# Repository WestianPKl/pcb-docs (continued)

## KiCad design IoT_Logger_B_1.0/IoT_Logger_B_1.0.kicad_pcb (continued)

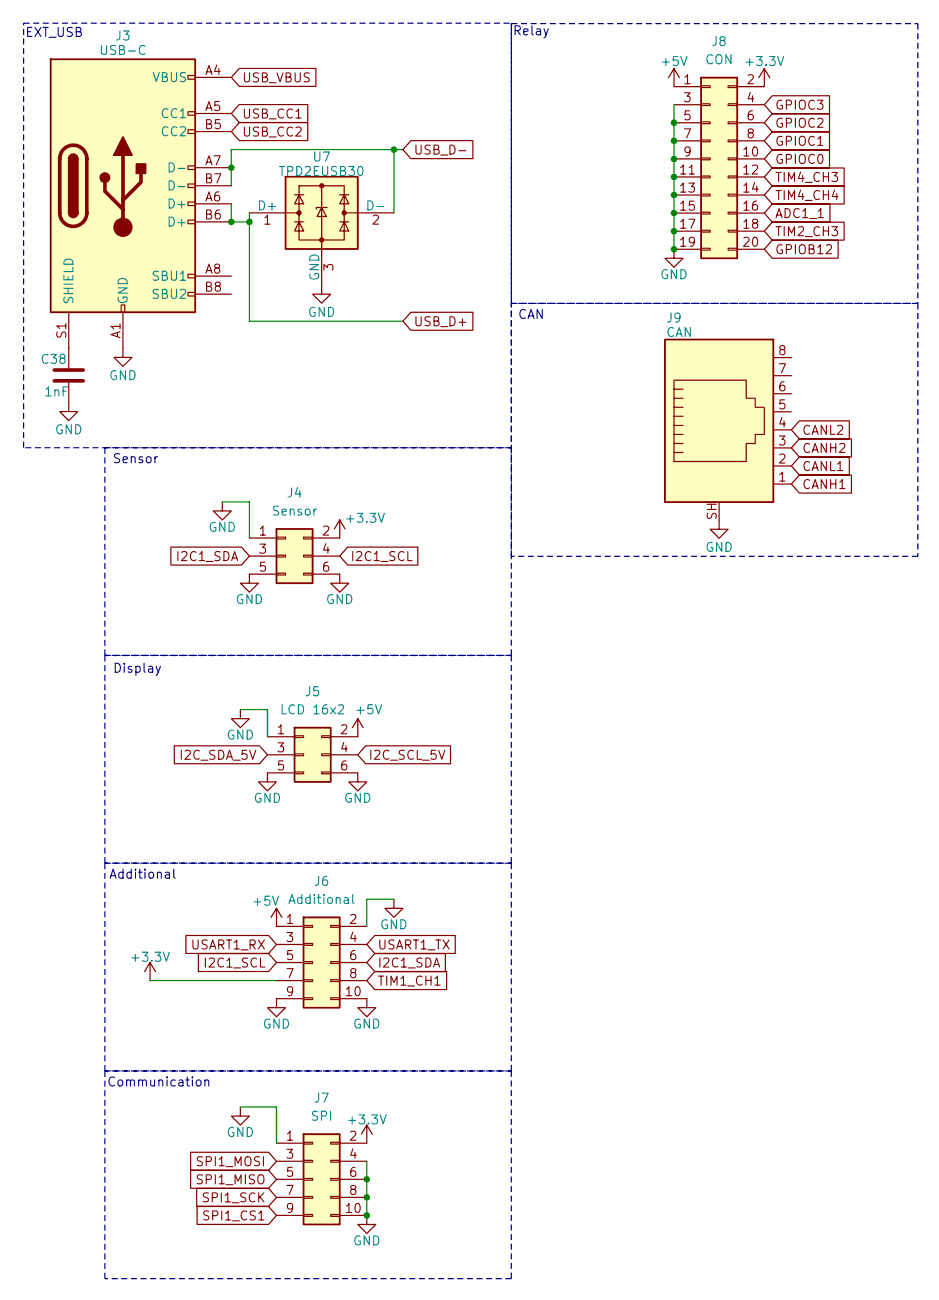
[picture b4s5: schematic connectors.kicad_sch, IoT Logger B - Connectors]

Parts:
C38: 1nF; C_0603_1608Metric
J3: USB-C; USB_C_Receptacle_GCT_USB4085
J4: Sensor; IDC-Header_2x03_P2.54mm_Vertical
J5: LCD 16x2; IDC-Header_2x03_P2.54mm_Vertical
J6: Additional; PinSocket_2x05_P2.54mm_Vertical
J7: SPI; IDC-Header_2x05_P2.54mm_Vertical
J8: CON; PinSocket_2x10_P2.54mm_Vertical
J9: CAN; RJ45_Amphenol_RJHSE5380_SHORT
U7: TPD2EUSB30; Texas_DRT-3

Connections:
+3.3V: J4.2, J6.7, J7.2, J8.2; also elsewhere on the board
+5V: J5.2, J6.1, J8.1; also elsewhere on the board
ADC1_1: J8.16; also elsewhere on the board
CANH1: J9.1; also elsewhere on the board
CANH2: J9.3
CANL1: J9.2; also elsewhere on the board
CANL2: J9.4
GND: C38.2, J3.A1 (GND), J3.A12 (GND), J3.B1 (GND), J3.B12 (GND), J4.1, J4.5, J4.6, J5.1, J5.5, J5.6, J6.2, J6.9, J6.10, J7.1, J7.4, J7.6, J7.8, J7.10, J8.3, J8.5, J8.7, J8.9, J8.11, J8.13, J8.15, J8.17, J8.19, J9.SH, U7.3 (GND); also elsewhere on the board
GPIOB12: J8.20; also elsewhere on the board
GPIOC0: J8.10; also elsewhere on the board
GPIOC1: J8.8; also elsewhere on the board
GPIOC2: J8.6; also elsewhere on the board
GPIOC3: J8.4; also elsewhere on the board
I2C1_SCL: J4.4, J6.5; also elsewhere on the board
I2C1_SDA: J4.3, J6.6; also elsewhere on the board
I2C_SCL_5V: J5.4; also elsewhere on the board
I2C_SDA_5V: J5.3; also elsewhere on the board
unnamed: C38.1, J3.S1 (SHIELD)
SPI1_CS1: J7.9; also elsewhere on the board
SPI1_MISO: J7.5; also elsewhere on the board
SPI1_MOSI: J7.3; also elsewhere on the board
SPI1_SCK: J7.7; also elsewhere on the board
TIM1_CH1: J6.8; also elsewhere on the board
TIM2_CH3: J8.18; also elsewhere on the board
TIM4_CH3: J8.12; also elsewhere on the board
TIM4_CH4: J8.14; also elsewhere on the board
USART1_RX: J6.3; also elsewhere on the board
USART1_TX: J6.4; also elsewhere on the board
USB_CC1: J3.A5 (CC1); also elsewhere on the board
USB_CC2: J3.B5 (CC2); also elsewhere on the board
USB_D+: J3.A6 (D+), J3.B6 (D+), U7.1 (D+); also elsewhere on the board
USB_D-: J3.A7 (D-), J3.B7 (D-), U7.2 (D-); also elsewhere on the board
USB_VBUS: J3.A4 (VBUS), J3.A9 (VBUS), J3.B4 (VBUS), J3.B9 (VBUS); also elsewhere on the board

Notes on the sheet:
EXT_USB
Additional
Sensor
Relay
CAN
Display
Communication

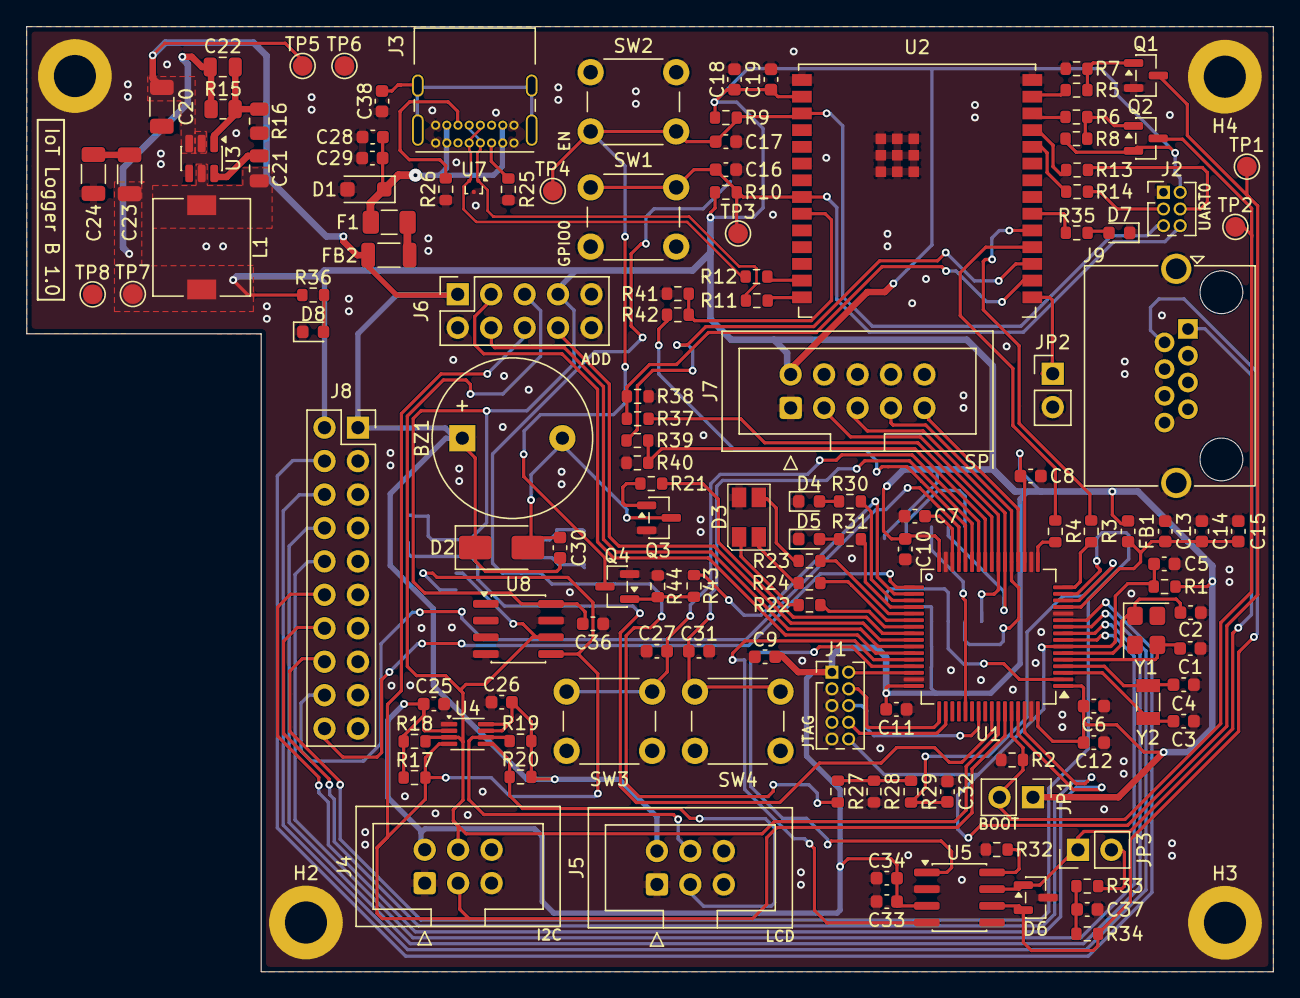
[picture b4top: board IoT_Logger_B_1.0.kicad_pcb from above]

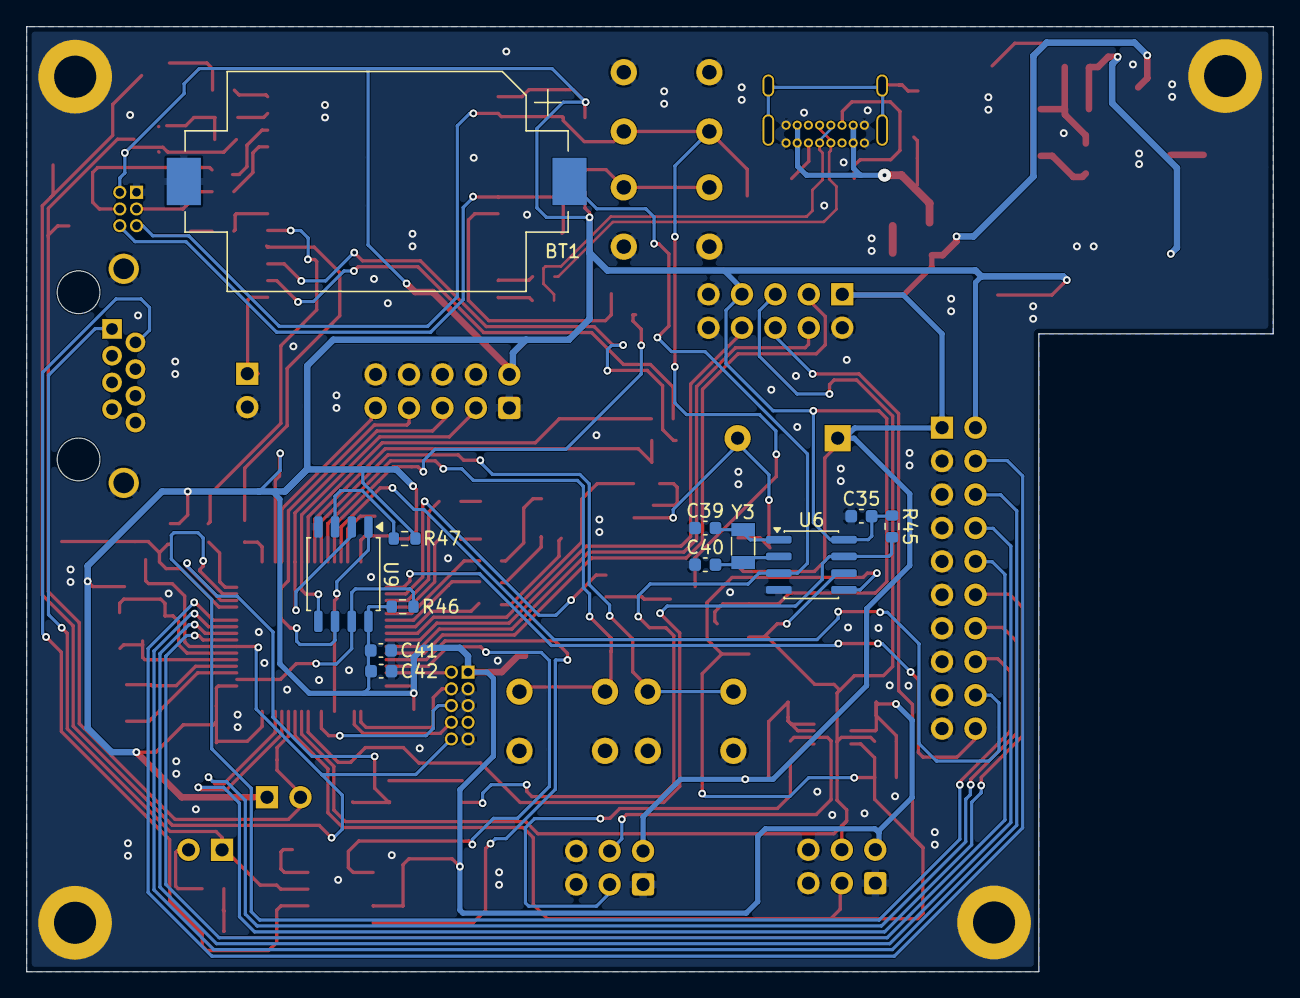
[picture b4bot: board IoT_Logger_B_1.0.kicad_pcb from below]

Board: 2 copper layers, 94.7 x 71.8 mm, 147 parts (12 on the bottom side), 105 nets.

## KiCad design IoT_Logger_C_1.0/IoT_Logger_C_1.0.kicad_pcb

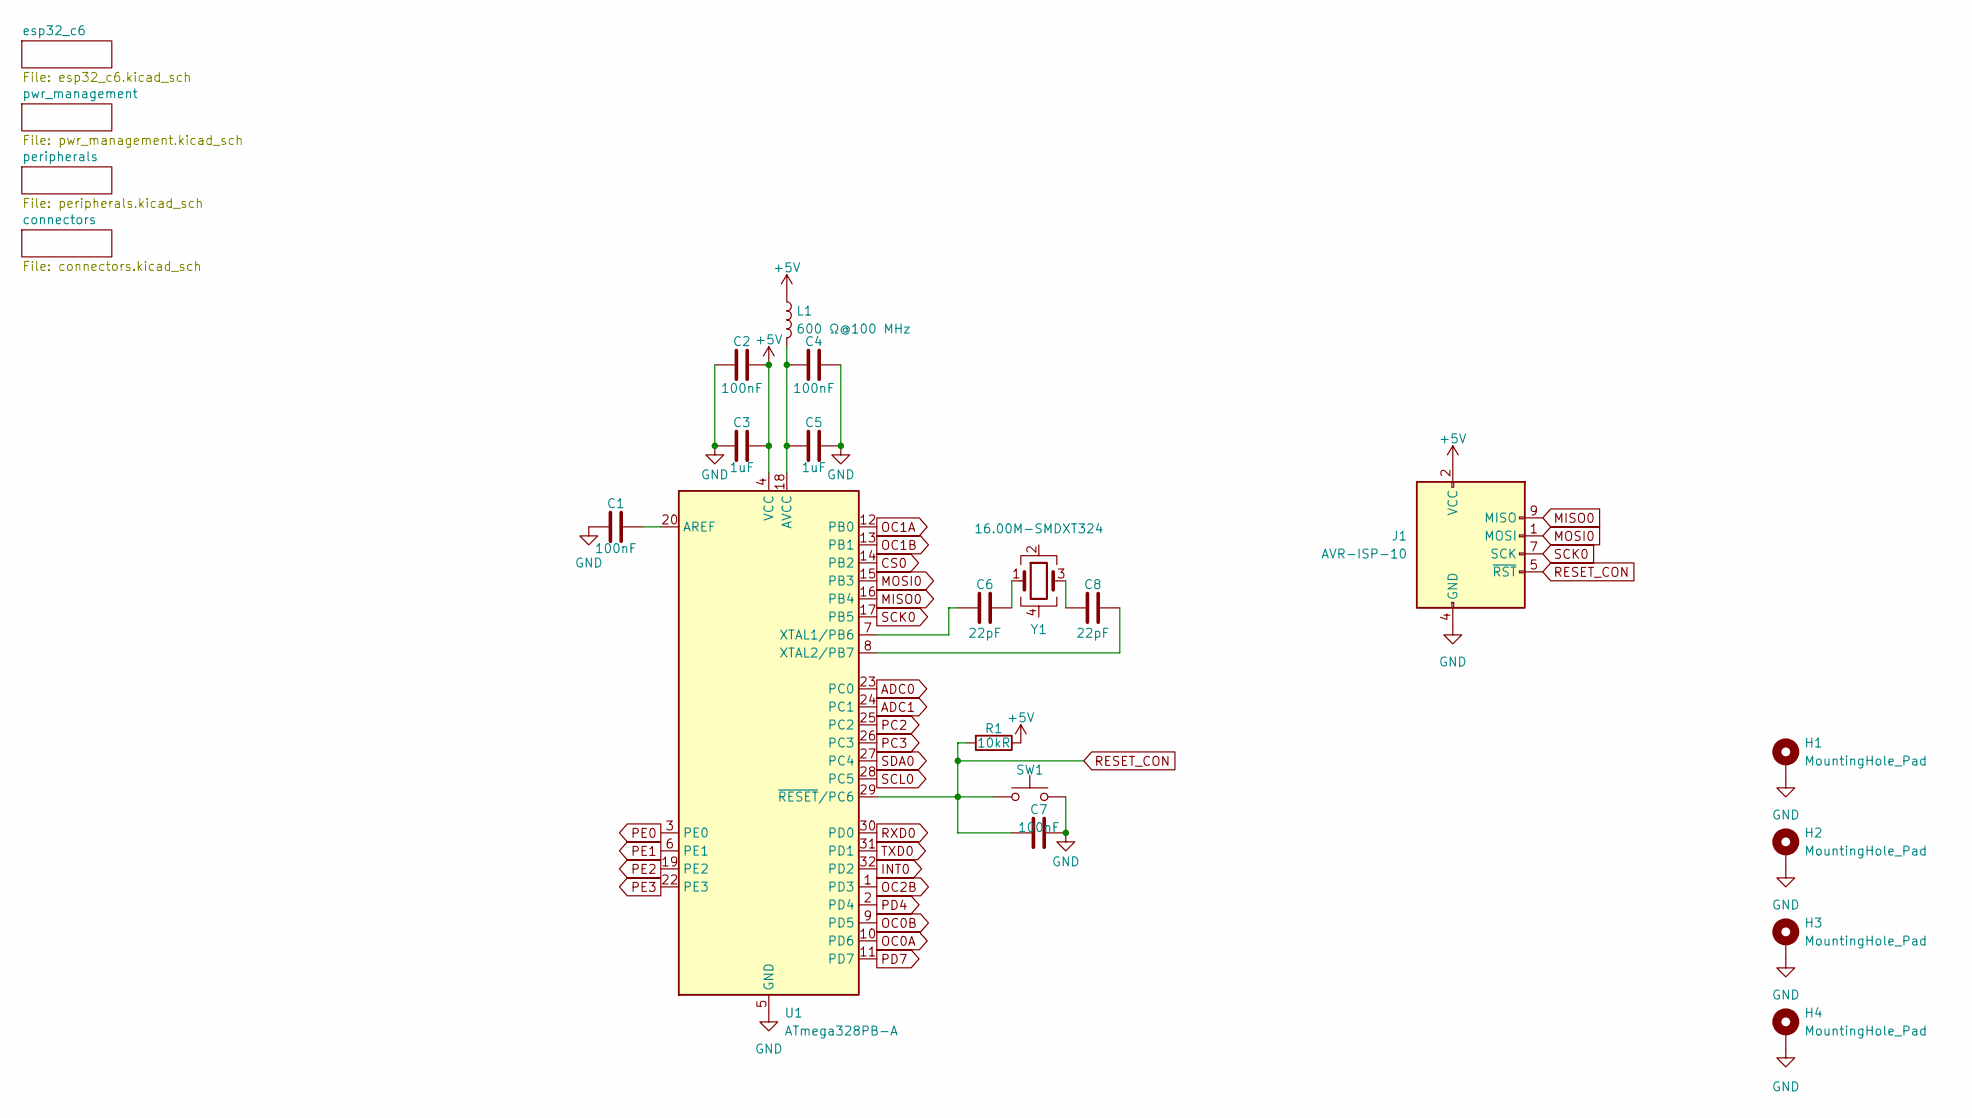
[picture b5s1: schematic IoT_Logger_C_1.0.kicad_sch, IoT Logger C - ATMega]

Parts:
C1, C2, C4, C7: 100nF; C_0603_1608Metric
C3, C5: 1uF; C_0603_1608Metric
C6, C8: 22pF; C_0603_1608Metric
H1, H2, H3, H4: MountingHole_Pad; MountingHole_3.2mm_M3_DIN965_Pad
J1: AVR-ISP-10; IDC-Header_2x05_P2.54mm_Vertical
L1: 600 Ω@100 MHz; L_0603_1608Metric
R1: 10kR; R_0603_1608Metric
SW1: Tact Switch 6x6mm / 13mm; SW_PUSH_6mm
U1: ATmega328PB-A; TQFP-32_7x7mm_P0.8mm
Y1: 16.00M-SMDXT324; Crystal_SMD_3225-4Pin_3.2x2.5mm

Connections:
+5V: C2.2, C3.2, J1.2 (VCC), L1.1, R1.1, U1.4 (VCC); also elsewhere on the board
ADC0: U1.23 (PC0); also elsewhere on the board
ADC1: U1.24 (PC1); also elsewhere on the board
CS0: U1.14 (PB2); also elsewhere on the board
GND: C1.1, C2.1, C3.1, C4.2, C5.2, C7.2, H1.1, H2.1, H3.1, H4.1, J1.4 (GND), J1.6 (GND), J1.8 (GND), J1.10 (GND), SW1.2, U1.5 (GND), U1.21 (GND); also elsewhere on the board
INT0: U1.32 (PD2); also elsewhere on the board
MISO0: J1.9 (MISO), U1.16 (PB4); also elsewhere on the board
MOSI0: J1.1 (MOSI), U1.15 (PB3); also elsewhere on the board
unnamed: C6.2, Y1.1
unnamed: C8.1, Y1.3
unnamed: C1.2, U1.20 (AREF)
unnamed: C4.1, C5.1, L1.2, U1.18 (AVCC)
unnamed: C6.1, U1.7 (XTAL1/PB6)
unnamed: C8.2, U1.8 (XTAL2/PB7)
OC0A: U1.10 (PD6); also elsewhere on the board
OC0B: U1.9 (PD5); also elsewhere on the board
OC1A: U1.12 (PB0); also elsewhere on the board
OC1B: U1.13 (PB1)
OC2B: U1.1 (PD3); also elsewhere on the board
PC2: U1.25 (PC2); also elsewhere on the board
PC3: U1.26 (PC3); also elsewhere on the board
PD4: U1.2 (PD4); also elsewhere on the board
PD7: U1.11 (PD7); also elsewhere on the board
PE0: U1.3 (PE0); also elsewhere on the board
PE1: U1.6 (PE1); also elsewhere on the board
PE2: U1.19 (PE2); also elsewhere on the board
PE3: U1.22 (PE3); also elsewhere on the board
RESET_CON: C7.1, J1.5 (~RST), R1.2, SW1.1, U1.29 (~RESET/PC6); also elsewhere on the board
RXD0: U1.30 (PD0); also elsewhere on the board
SCK0: J1.7 (SCK), U1.17 (PB5); also elsewhere on the board
SCL0: U1.28 (PC5); also elsewhere on the board
SDA0: U1.27 (PC4); also elsewhere on the board
TXD0: U1.31 (PD1); also elsewhere on the board

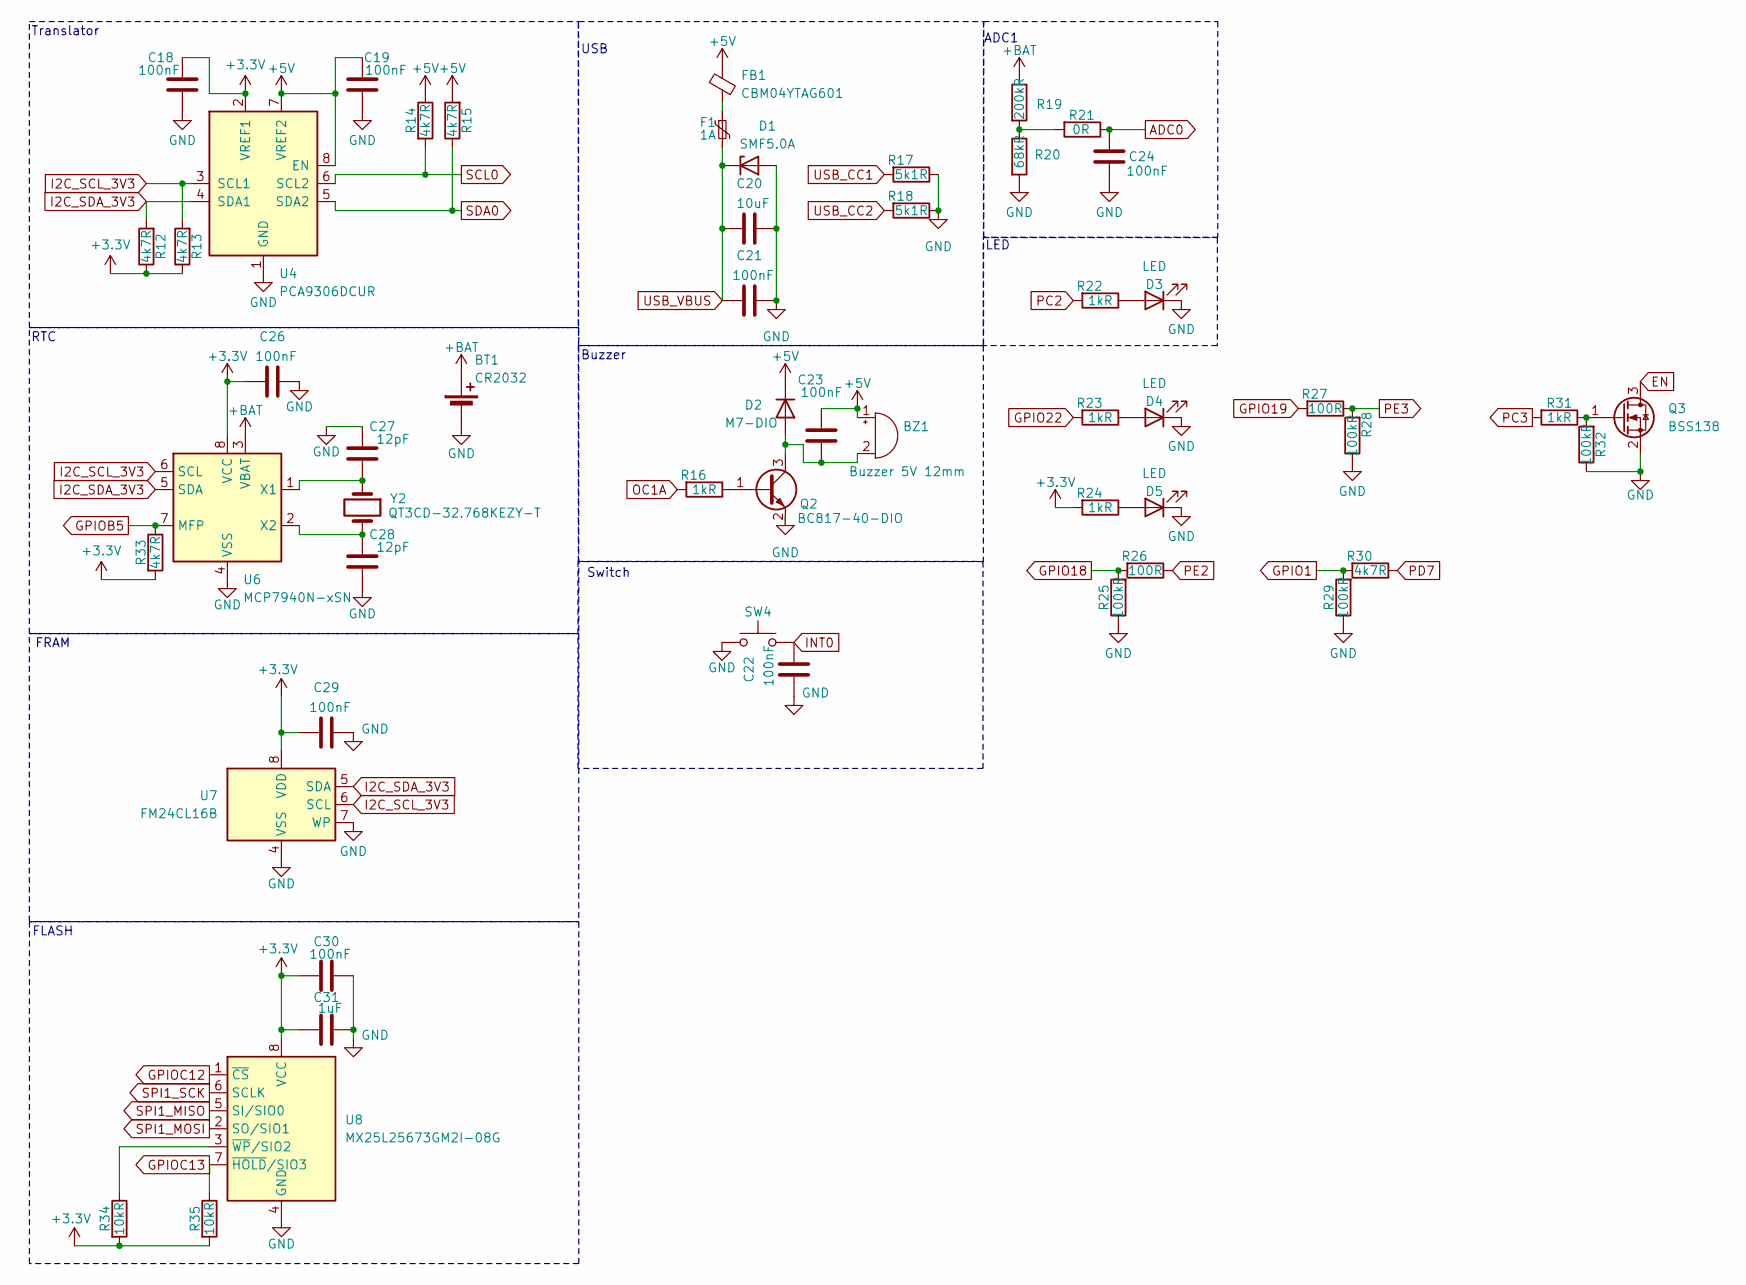
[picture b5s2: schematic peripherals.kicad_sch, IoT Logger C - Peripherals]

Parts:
BT1: CR2032; BatteryHolder_Keystone_1060_1x2032
BZ1: Buzzer 5V 12mm; Buzzer_12x9.5RM7.6
C18, C19, C21, C22, C23, C24, C26, C29, C30: 100nF; C_0603_1608Metric
C20: 10uF; C_0603_1608Metric
C27, C28: 12pF; C_0603_1608Metric
C31: 1uF; C_0603_1608Metric
D1: SMF5.0A; D_SOD-123F
D2: M7-DIO; D_SMA
D3, D4, D5: LED; LED_0603_1608Metric
F1: 1A; Fuse_1206_3216Metric
FB1: CBM04YTAG601; L_1206_3216Metric
Q2: BC817-40-DIO; SOT-23
Q3: BSS138; SOT-23
R12, R13, R14, R15, R30, R33: 4k7R; R_0603_1608Metric
R16, R22, R23, R24, R31: 1kR; R_0603_1608Metric
R17, R18: 5k1R; R_0603_1608Metric
R19: 200kR; R_0603_1608Metric
R20: 68kR; R_0603_1608Metric
R21: 0R; R_0603_1608Metric
R25, R28, R29, R32: 100kR; R_0603_1608Metric
R26, R27: 100R; R_0603_1608Metric
R34, R35: 10kR; R_0603_1608Metric
SW4: Tact Switch 6x6mm / 13mm; SW_PUSH_6mm
U4: PCA9306DCUR; VSSOP-8_2.3x2mm_P0.5mm
U6: MCP7940N-xSN; SOIC-8_3.9x4.9mm_P1.27mm
U7: FM24CL16B; SOIC-8_3.9x4.9mm_P1.27mm
U8: MX25L25673GM2I-08G; SOIC-8_5.3x5.3mm_P1.27mm
Y2: QT3CD-32.768KEZY-T; Crystal_SMD_3215-2Pin_3.2x1.5mm

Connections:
+3.3V: C18.1, C26.2, C29.2, C30.2, C31.2, R12.1, R13.1, R24.2, R33.2, R34.2, R35.2, U4.2 (VREF1), U6.8 (VCC), U7.8 (VDD), U8.8 (VCC); also elsewhere on the board
+5V: BZ1.1 (+), C19.1, C23.2, D2.1 (K), FB1.1, R14.1, R15.2, U4.7 (VREF2), U4.8 (EN); also elsewhere on the board
+BAT: BT1.1 (+), R19.1, U6.3 (VBAT)
ADC0: C24.1, R21.1; also elsewhere on the board
EN: Q3.3 (D); also elsewhere on the board
GND: BT1.2 (-), C18.2, C19.2, C20.1, C21.1, C22.2, C24.2, C26.1, C27.2, C28.1, C29.1, C30.1, C31.1, D1.2 (A), D3.1 (K), D4.1 (K), D5.1 (K), Q2.2 (E), Q3.2 (S), R17.1, R18.1, R20.2, R25.1, R28.1, R29.1, R32.1, SW4.1, U4.1 (GND), U6.4 (VSS), U7.4 (VSS), U7.7 (WP), U8.4 (GND); also elsewhere on the board
GPIO1: R29.2, R30.2; also elsewhere on the board
GPIO18: R25.2, R26.2; also elsewhere on the board
GPIO19: R27.2; also elsewhere on the board
GPIO22: R23.2; also elsewhere on the board
GPIOB5: R33.1, U6.7 (MFP)
I2C_SCL_3V3: R13.2, U4.3 (SCL1), U6.6 (SCL), U7.6 (SCL); also elsewhere on the board
I2C_SDA_3V3: R12.2, U4.4 (SDA1), U6.5 (SDA), U7.5 (SDA); also elsewhere on the board
INT0: C22.1, SW4.2; also elsewhere on the board
unnamed: BZ1.2 (-), C23.1, D2.2 (A), Q2.3 (C)
unnamed: D3.2 (A), R22.1
unnamed: D4.2 (A), R23.1
unnamed: D5.2 (A), R24.1
unnamed: F1.1, FB1.2
unnamed: Q2.1 (B), R16.1
unnamed: Q3.1 (G), R31.1, R32.2
unnamed: R19.2, R20.1, R21.2
unnamed: R34.1, U8.3 (~WP/SIO2)
unnamed: R35.1, U8.7 (~HOLD/SIO3)
unnamed: C27.1, U6.1 (X1), Y2.1
unnamed: C28.2, U6.2 (X2), Y2.2
OC1A: R16.2; also elsewhere on the board
PC2: R22.2; also elsewhere on the board
PC3: R31.2; also elsewhere on the board
PD7: R30.1; also elsewhere on the board
PE2: R26.1; also elsewhere on the board
PE3: R27.1, R28.2; also elsewhere on the board
SCL0: R14.2, U4.6 (SCL2); also elsewhere on the board
SDA0: R15.1, U4.5 (SDA2); also elsewhere on the board
USB_CC1: R17.2; also elsewhere on the board
USB_CC2: R18.2; also elsewhere on the board
USB_VBUS: C20.2, C21.2, D1.1 (K), F1.2; also elsewhere on the board

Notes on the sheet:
USB
RTC
FRAM
FLASH
Switch
Translator
Buzzer
ADC1
LED

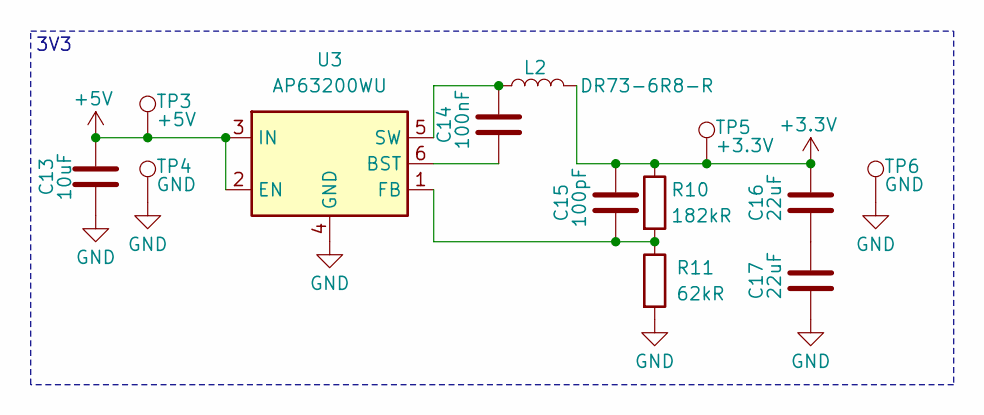
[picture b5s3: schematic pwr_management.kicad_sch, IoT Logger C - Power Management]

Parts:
C13: 10uF; C_1206_3216Metric
C14: 100nF; C_0805_2012Metric
C15: 100pF; C_0805_2012Metric
C16, C17: 22uF; C_1206_3216Metric
L2: DR73-6R8-R; L_7.3x7.3_H3.5
R10: 182kR; R_0805_2012Metric
R11: 62kR; R_0805_2012Metric
TP3: +5V; TestPoint_Pad_D1.5mm
TP4, TP6: GND; TestPoint_Pad_D1.5mm
TP5: +3.3V; TestPoint_Pad_D1.5mm
U3: AP63200WU; TSOT-23-6

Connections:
+3.3V: C15.1, C16.1, L2.2, R10.1, TP5.1; also elsewhere on the board
+5V: C13.1, TP3.1, U3.2 (EN), U3.3 (IN); also elsewhere on the board
GND: C13.2, C17.2, R11.2, TP4.1, TP6.1, U3.4 (GND); also elsewhere on the board
unnamed: C16.2, C17.1
unnamed: C14.2, U3.6 (BST)
unnamed: C15.2, R10.2, R11.1, U3.1 (FB)
unnamed: C14.1, L2.1, U3.5 (SW)

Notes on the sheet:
3V3

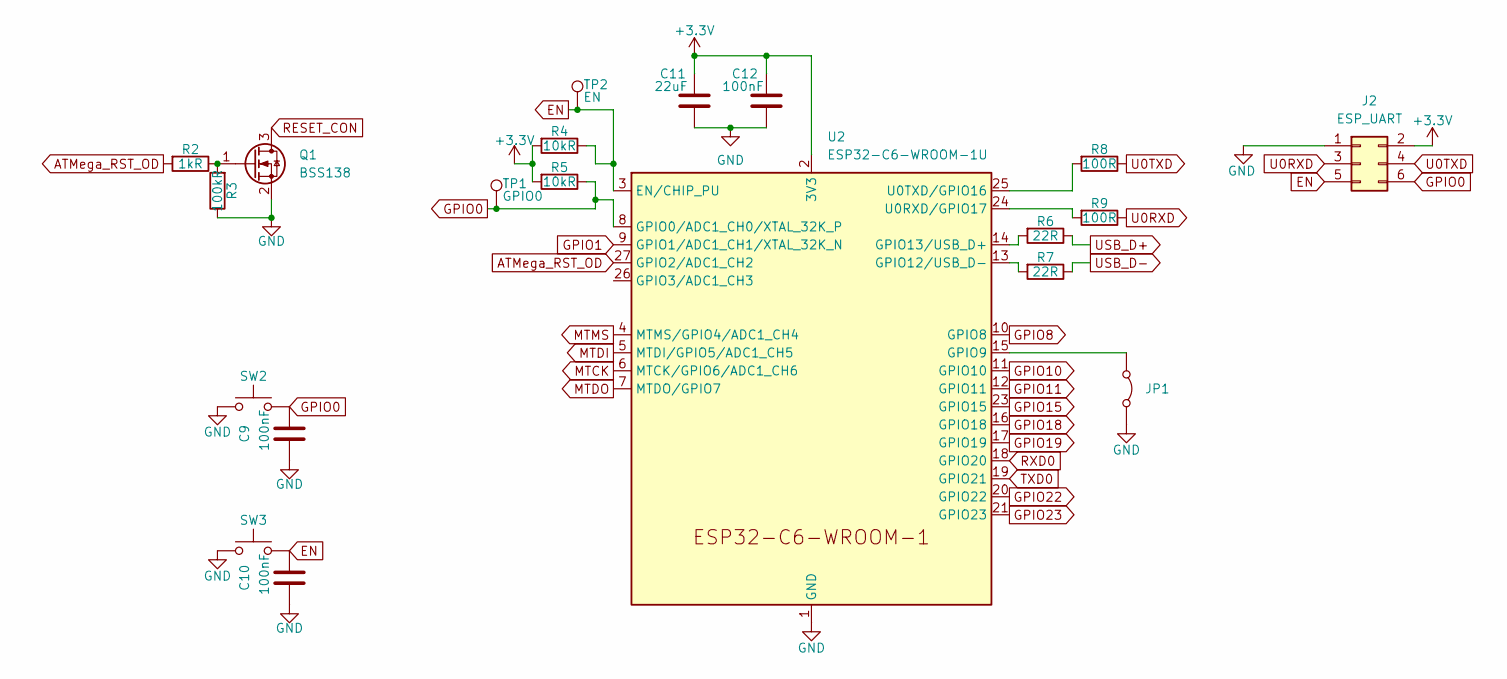
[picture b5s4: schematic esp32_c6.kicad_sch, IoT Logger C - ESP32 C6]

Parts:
C9, C10, C12: 100nF; C_0603_1608Metric
C11: 22uF; C_0603_1608Metric
J2: ESP_UART; PinHeader_2x03_P1.27mm_Vertical
JP1: Jumper_2_Bridged; PinHeader_1x02_P2.54mm_Vertical
Q1: BSS138; SOT-23
R2: 1kR; R_0603_1608Metric
R3: 100kR; R_0603_1608Metric
R4, R5: 10kR; R_0603_1608Metric
R6, R7: 22R; R_0603_1608Metric
R8, R9: 100R; R_0603_1608Metric
SW2, SW3: Tact Switch 6x6mm / 13mm; SW_PUSH_6mm
TP1: GPIO0; TestPoint_Pad_D1.5mm
TP2: EN; TestPoint_Pad_D1.5mm
U2: ESP32-C6-WROOM-1U

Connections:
+3.3V: C11.1, C12.1, J2.2, R4.2, R5.2, U2.2 (3V3); also elsewhere on the board
ATMega_RST_OD: R2.2, U2.27 (GPIO2/ADC1_CH2)
EN: C10.1, J2.5, R4.1, SW3.2, TP2.1, U2.3 (EN/CHIP_PU); also elsewhere on the board
GND: C9.2, C10.2, C11.2, C12.2, J2.1, JP1.2 (B), Q1.2 (S), R3.1, SW2.1, SW3.1, U2.1 (GND), U2.28 (GND), U2.29 (GND); also elsewhere on the board
GPIO0: C9.1, J2.6, R5.1, SW2.2, TP1.1, U2.8 (GPIO0/ADC1_CH0/XTAL_32K_P)
GPIO1: U2.9 (GPIO1/ADC1_CH1/XTAL_32K_N); also elsewhere on the board
GPIO8: U2.10 (GPIO8)
GPIO10: U2.11 (GPIO10)
GPIO11: U2.12 (GPIO11)
GPIO15: U2.23 (GPIO15)
GPIO18: U2.16 (GPIO18); also elsewhere on the board
GPIO19: U2.17 (GPIO19); also elsewhere on the board
GPIO22: U2.20 (GPIO22); also elsewhere on the board
GPIO23: U2.21 (GPIO23)
MTCK: U2.6 (MTCK/GPIO6/ADC1_CH6)
MTDI: U2.5 (MTDI/GPIO5/ADC1_CH5)
MTDO: U2.7 (MTDO/GPIO7)
MTMS: U2.4 (MTMS/GPIO4/ADC1_CH4)
unnamed: JP1.1 (A), U2.15 (GPIO9)
unnamed: Q1.1 (G), R2.1, R3.2
unnamed: R7.2, U2.13 (GPIO12/USB_D-)
unnamed: R6.2, U2.14 (GPIO13/USB_D+)
unnamed: R9.2, U2.24 (U0RXD/GPIO17)
unnamed: R8.2, U2.25 (U0TXD/GPIO16)
RESET_CON: Q1.3 (D); also elsewhere on the board
RXD0: U2.18 (GPIO20); also elsewhere on the board
TXD0: U2.19 (GPIO21); also elsewhere on the board
U0RXD: J2.3, R9.1
U0TXD: J2.4, R8.1
USB_D+: R6.1; also elsewhere on the board
USB_D-: R7.1; also elsewhere on the board

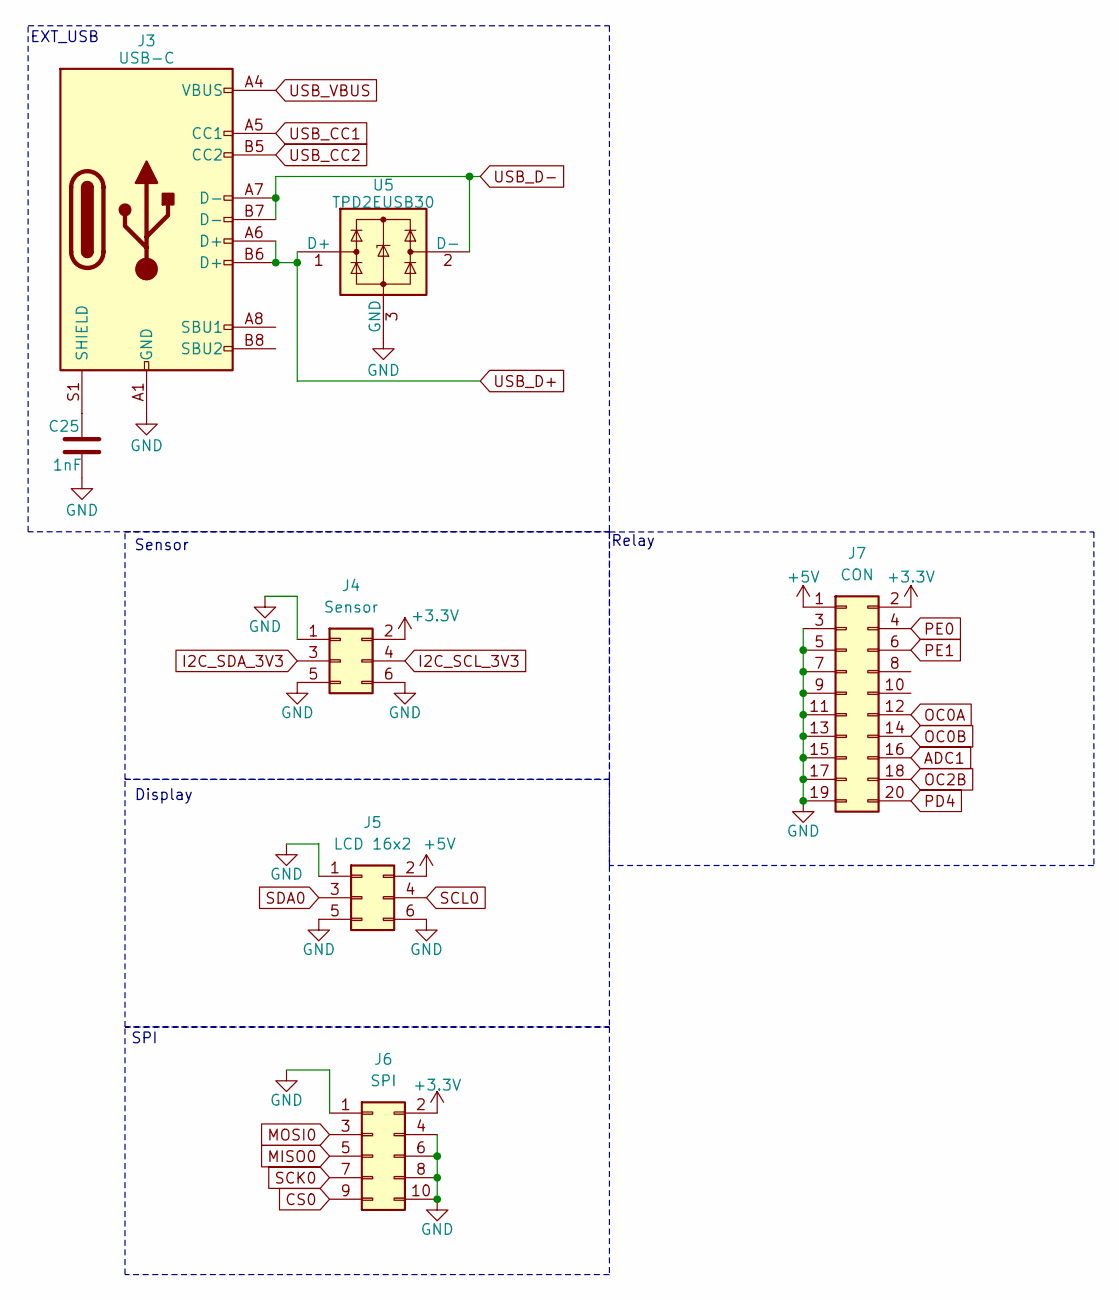
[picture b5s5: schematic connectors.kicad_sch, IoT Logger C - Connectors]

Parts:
C25: 1nF; C_0603_1608Metric
J3: USB-C; USB_C_Receptacle_GCT_USB4085
J4: Sensor; IDC-Header_2x03_P2.54mm_Vertical
J5: LCD 16x2; IDC-Header_2x03_P2.54mm_Vertical
J6: SPI; IDC-Header_2x05_P2.54mm_Vertical
J7: CON; PinSocket_2x10_P2.54mm_Vertical
U5: TPD2EUSB30; Texas_DRT-3

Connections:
+3.3V: J4.2, J6.2, J7.2; also elsewhere on the board
+5V: J5.2, J7.1; also elsewhere on the board
ADC1: J7.16; also elsewhere on the board
CS0: J6.9; also elsewhere on the board
GND: C25.2, J3.A1 (GND), J3.A12 (GND), J3.B1 (GND), J3.B12 (GND), J4.1, J4.5, J4.6, J5.1, J5.5, J5.6, J6.1, J6.4, J6.6, J6.8, J6.10, J7.3, J7.5, J7.7, J7.9, J7.11, J7.13, J7.15, J7.17, J7.19, U5.3 (GND); also elsewhere on the board
I2C_SCL_3V3: J4.4; also elsewhere on the board
I2C_SDA_3V3: J4.3; also elsewhere on the board
MISO0: J6.5; also elsewhere on the board
MOSI0: J6.3; also elsewhere on the board
unnamed: C25.1, J3.S1 (SHIELD)
OC0A: J7.12; also elsewhere on the board
OC0B: J7.14; also elsewhere on the board
OC2B: J7.18; also elsewhere on the board
PD4: J7.20; also elsewhere on the board
PE0: J7.4; also elsewhere on the board
PE1: J7.6; also elsewhere on the board
SCK0: J6.7; also elsewhere on the board
SCL0: J5.4; also elsewhere on the board
SDA0: J5.3; also elsewhere on the board
USB_CC1: J3.A5 (CC1); also elsewhere on the board
USB_CC2: J3.B5 (CC2); also elsewhere on the board
USB_D+: J3.A6 (D+), J3.B6 (D+), U5.1 (D+); also elsewhere on the board
USB_D-: J3.A7 (D-), J3.B7 (D-), U5.2 (D-); also elsewhere on the board
USB_VBUS: J3.A4 (VBUS), J3.A9 (VBUS), J3.B4 (VBUS), J3.B9 (VBUS); also elsewhere on the board

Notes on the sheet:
EXT_USB
Sensor
Relay
Display
SPI

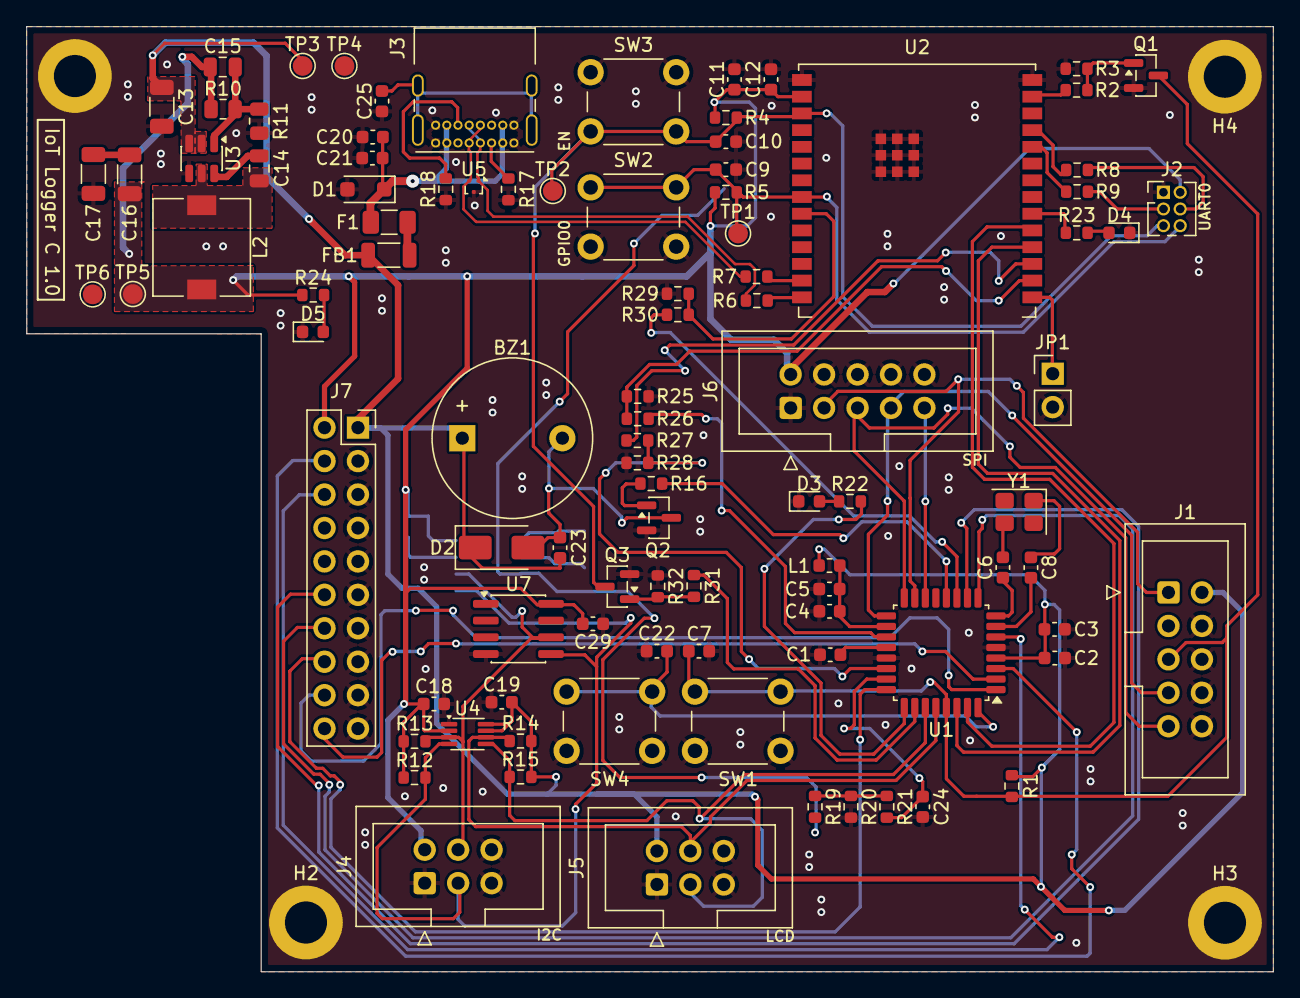
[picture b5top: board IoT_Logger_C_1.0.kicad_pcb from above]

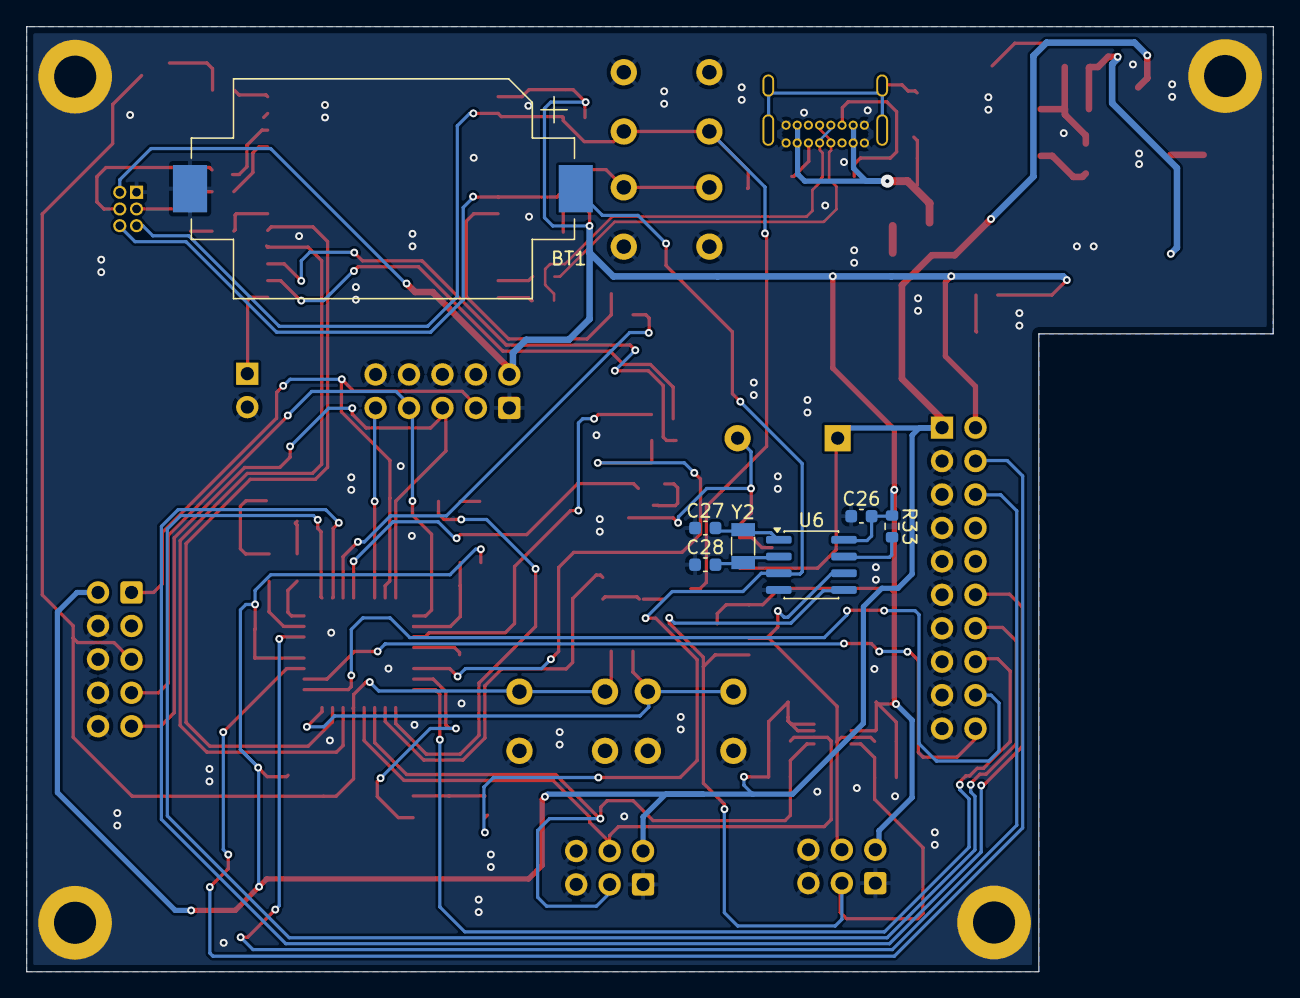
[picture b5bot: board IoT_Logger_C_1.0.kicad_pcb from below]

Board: 2 copper layers, 94.7 x 71.8 mm, 107 parts (7 on the bottom side), 72 nets.
